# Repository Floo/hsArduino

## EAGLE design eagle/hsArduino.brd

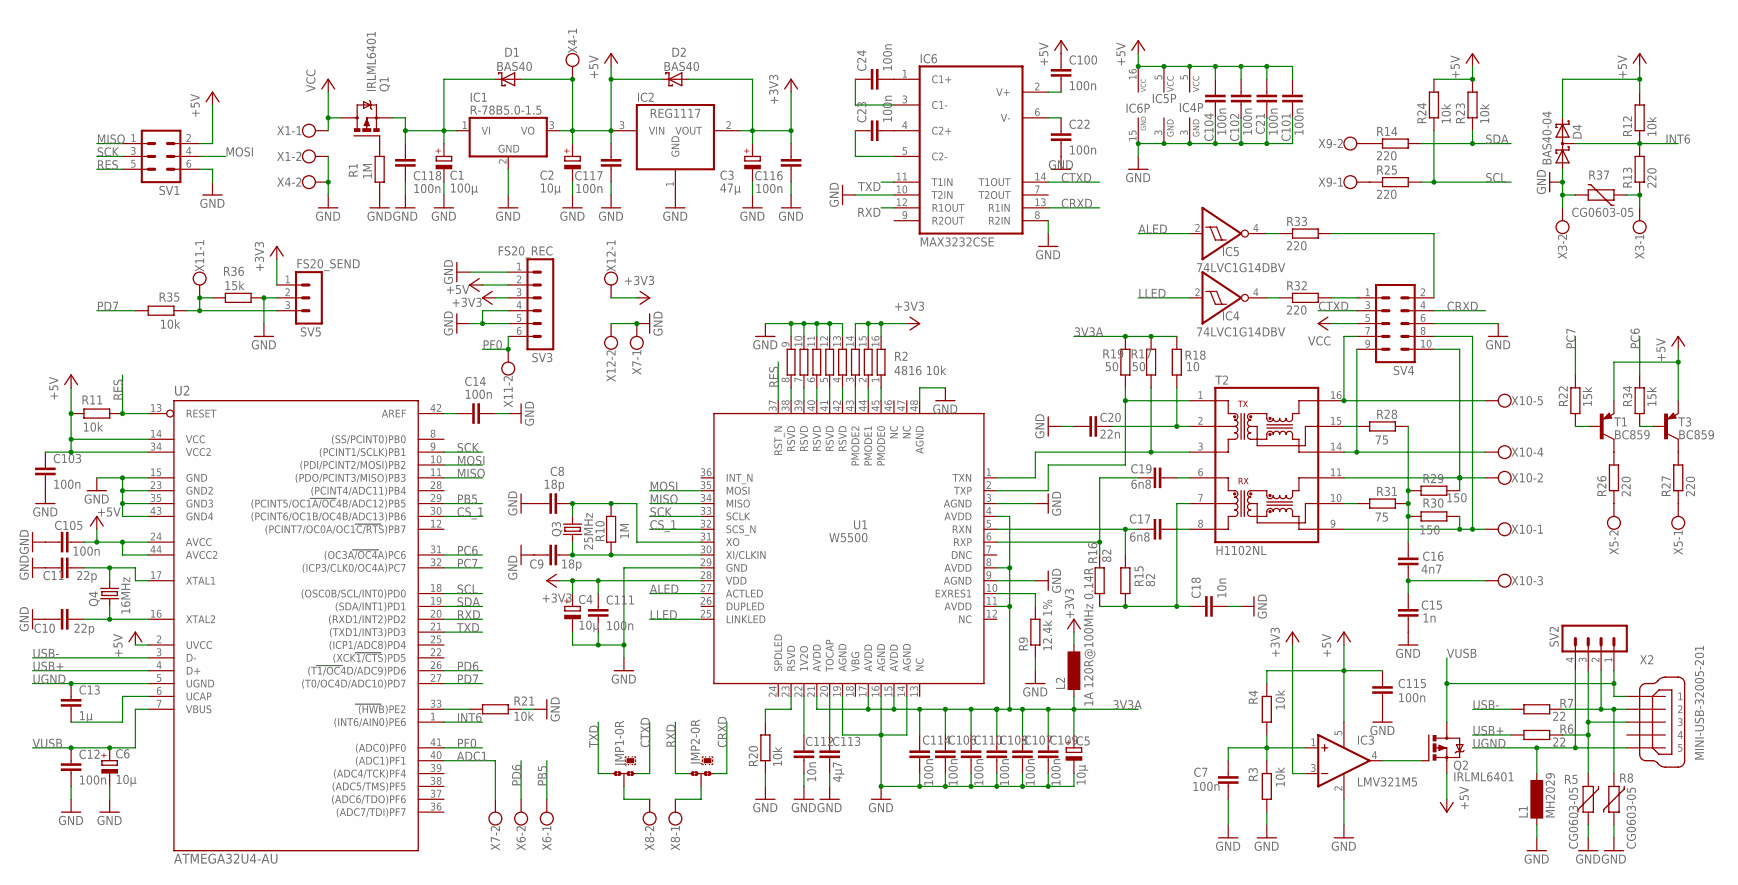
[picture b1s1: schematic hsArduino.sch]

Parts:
C1: 100µ; E2,5-7
C2, C4, C5, C6: 10µ; E2-5
C3: 47µ; E2-5
C7, C12, C14, C21, C22, C23, C24, C100, C101, C102, C103, C104, C105, C106, C107, C108, C109, C110, C111, C114, C115, C116, C117, C118: 100n; C0805K
C8, C9: 18p; C0805K
C10, C11: 22p; C0805K
C13: 1µ; C0805K
C15: 1n; C0805K
C16: 4n7; C0805K
C17, C19: 6n8; C0805K
C18, C112: 10n; C0805K
C20: 22n; C0805K
C113: 4µ7; C0805K
D1, D2: BAS40; SOT23
D4: BAS40-04; SOT23
IC1: R-78B5.0-1.5; TO220V
IC2: REG1117; SOT223
IC3: LMV321M5; SOT23-5
IC4, IC5: 74LVC1G14DBV; SOT23-5
IC6: MAX3232CSE; SO16
JMP1, JMP2: 0R-JUMPA; A0R-JMP
L1: MH2029; SM-1206
L2: 1A 120R@100MHz 0.14R; SM-1206
Q1, Q2: IRLML6401; MICRO3
Q3: 25MHz; HC49/S
Q4: 16MHz; HC49/S
R1, R10: 1M; R0805
R2: 4816 10k; 4816P
R3, R4, R11, R12, R20, R21, R23, R24, R35: 10k; R0805
R5, R8, R37: CG0603-05; CT/CN0603
R6, R7: 22; R0805
R9: 12.4k 1%; R0805
R13, R14, R25, R26, R27, R32, R33: 220; R0805
R15, R16: 82; R0805
R17, R19: 50; R0805
R18: 10; R0805
R22, R34, R36: 15k; R0805
R28, R31: 75; R0805
R29, R30: 150; R0805
SV1: ML6
SV2: MA04-1
SV3: FS20_REC; MA06-1
SV4: ML10
SV5: FS20_SEND; MA03-1
T1, T3: BC859; SOT23-BEC
T2: H1102NL; HXXXX
U1: W5500
U2: ATMEGA32U4-AU; TQFP44
X1, X3, X4, X5, X6, X7, X8, X9, X11, X12: W237-02P; W237-132
X2: MINI-USB-32005-201; 32005-201
X10: W237-05P; W237-5P

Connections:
3V3A: C5.+, C106.1, C107.1, C108.1, C109.1, C110.1, C114.1, L2.1, R17.2, R18.2, R19.2, U1.4 (AVDD), U1.8 (AVDD), U1.11 (AVDD), U1.15 (AVDD), U1.17 (AVDD), U1.21 (AVDD)
+3V3: C3.+, C4.+, C111.1, C116.2, D2.1 (A), IC2.2 (VOUT), IC3.3 (-IN), L2.2, R2.14, R2.15, R2.16, SV3.3, SV5.1, U1.28 (VDD), X12.1
+5V: C2.+, C21.1, C100.1, C101.1, C102.2, C103.1, C104.2, C105.1, C115.2, C117.2, D1.1 (A), D2.3 (C), D4.2 (C2), IC1.3 (VO), IC2.3 (VIN), IC3.5 (V+), IC4.5 (VCC), IC5.5 (VCC), IC6.16 (VCC), Q2.2 (S), R4.1, R11.2, R12.2, R23.2, R24.2, SV1.2, SV3.2, T1.E, T3.E, U2.2 (UVCC), U2.14 (VCC), U2.24 (AVCC), U2.34 (VCC2), U2.44 (AVCC2), X4.1
ADC1: U2.40 ((ADC1)PF1), X7.2
ALED: IC5.2 (I), U1.27 (ACTLED)
CRXD: IC6.13 (R1IN), JMP2.1, SV4.4
CS_1: U1.32 (SCS_N), U2.30 ((PCINT6/OC1B/OC4B/ADC13)PB6)
CTXD: IC6.14 (T1OUT), JMP1.1, SV4.3
GND: C1.-, C2.-, C3.-, C4.-, C5.-, C6.-, C7.2, C8.1, C9.2, C10.2, C11.1, C12.2, C14.2, C15.1, C18.2, C20.1, C21.2, C22.2, C101.2, C102.1, C103.2, C104.1, C105.2, C106.2, C107.2, C108.2, C109.2, C110.2, C111.2, C112.2, C113.2, C114.2, C115.1, C116.1, C117.1, C118.2, D4.1 (A1), IC1.2 (GND), IC2.1 (GND), IC3.2 (V-), IC4.3 (GND), IC5.3 (GND), IC6.8 (R2IN), IC6.10 (T2IN), IC6.15 (GND), L1.1, R1.2, R2.9, R2.10, R2.11, R2.12, R2.13, R3.2, R5.2, R8.2, R9.1, R20.1, R21.2, R36.1, R37.2, SV1.6, SV3.1, SV3.4, SV3.5, SV4.6, SV5.2, U1.3 (AGND), U1.9 (AGND), U1.14 (AGND), U1.16 (AGND), U1.19 (AGND), U1.29 (GND), U1.48 (AGND), U2.15 (GND), U2.23 (GND2), U2.35 (GND3), U2.43 (GND4), X1.2, X3.2, X4.2, X7.1, X12.2
INT6: D4.3 (C1A2), R12.1, R13.2, U2.1 ((INT6/AIN0)PE6)
LLED: IC4.2 (I), U1.25 (LINKLED)
MISO: SV1.1, U1.34 (MISO), U2.11 ((PDO/PCINT3/MISO)PB3)
MOSI: SV1.4, U1.35 (MOSI), U2.10 ((PDI/PCINT2/MOSI)PB2)
unnamed: C10.1, Q4.2, U2.16 (XTAL2)
unnamed: C11.2, Q4.1, U2.17 (XTAL1)
unnamed: C17.1, R15.1, U1.5 (RXN)
unnamed: C1.+, C118.1, D1.3 (C), IC1.1 (VI), Q1.2 (S)
unnamed: C113.1, U1.20 (TOCAP)
unnamed: C19.1, R16.1, U1.6 (RXP)
unnamed: C9.1, Q3.2, R10.2, U1.30 (XI/CLKIN)
unnamed: R35.1, R36.2, SV5.3, X11.1
unnamed: JMP1.2, X8.2
unnamed: C20.2, R18.1, T2.2
unnamed: Q1.1 (G), R1.1
unnamed: C8.2, Q3.1, R10.1, U1.31 (XO)
unnamed: R19.1, T2.1, U1.2 (TXP)
unnamed: R2.8, U1.38 (RSVD)
unnamed: R20.2, U1.23 (RSVD)
unnamed: C18.1, R15.2, R16.2, T2.7
unnamed: R17.1, T2.3, U1.1 (TXN)
unnamed: C19.2, T2.6
unnamed: SV4.7, T2.16, X10.5
unnamed: C112.1, U1.22 (1V2O)
unnamed: SV4.9, T2.14, X10.4
unnamed: R29.1, SV4.10, T2.11, X10.2
unnamed: R28.2, T2.15
unnamed: C15.2, C16.1, X10.3
unnamed: R2.7, U1.39 (RSVD)
unnamed: JMP2.2, X8.1
unnamed: R33.2, SV4.2
unnamed: R9.2, U1.10 (EXRES1)
unnamed: C14.1, U2.42 (AREF)
unnamed: R2.6, U1.40 (RSVD)
unnamed: R2.5, U1.41 (RSVD)
unnamed: R2.4, U1.42 (RSVD)
unnamed: C17.2, T2.8
unnamed: R2.3, U1.43 (PMODE2)
unnamed: R2.2, U1.44 (PMODE1)
unnamed: R2.1, U1.45 (PMODE0)
unnamed: C16.2, R28.1, R29.2, R30.2, R31.1
unnamed: R13.1, R37.1, X3.1
unnamed: R31.2, T2.10
unnamed: R30.1, SV4.8, T2.9, X10.1
unnamed: IC5.4 (O), R33.1
unnamed: IC4.4 (O), R32.1
unnamed: R21.1, U2.33 ((HWB)PE2)
unnamed: R26.1, X5.2
unnamed: R32.2, SV4.1
unnamed: R27.1, X5.1
unnamed: C24.1, IC6.3 (C1-)
unnamed: R7.1, R8.1, SV2.2, X2.2
unnamed: C24.2, IC6.1 (C1+)
unnamed: C23.2, IC6.4 (C2+)
unnamed: C23.1, IC6.5 (C2-)
unnamed: C22.1, IC6.6 (V-)
unnamed: C100.2, IC6.2 (V+)
unnamed: R26.2, T1.C
unnamed: R5.1, R6.1, SV2.3, X2.3
unnamed: R27.2, T3.C
unnamed: R22.1, T1.B
unnamed: R34.1, T3.B
unnamed: C13.2, U2.6 (UCAP)
unnamed: C7.1, IC3.1 (+IN), R3.1, R4.2
unnamed: IC3.4 (OUT), Q2.1 (G)
unnamed: R14.1, X9.2
unnamed: R25.1, X9.1
PB5: U2.29 ((PCINT5/OC1A/OC4B/ADC12)PB5), X6.1
PC6: R34.2, U2.31 ((OC3A/OC4A)PC6)
PC7: R22.2, U2.32 ((ICP3/CLK0/OC4A)PC7)
PD6: U2.26 ((T1/OC4D/ADC9)PD6), X6.2
PD7: R35.2, U2.27 ((T0/OC4D/ADC10)PD7)
PF0: SV3.6, U2.41 ((ADC0)PF0), X11.2
RES: R11.1, SV1.5, U1.37 (RST_N), U2.13 (RESET)
RXD: IC6.12 (R1OUT), JMP2.3, U2.20 ((RXD1/INT2)PD2)
SCK: SV1.3, U1.33 (SCLK), U2.9 ((PCINT1/SCLK)PB1)
SCL: R24.1, R25.2, U2.18 ((OSC0B/SCL/INT0)PD0)
SDA: R14.2, R23.1, U2.19 ((SDA/INT1)PD1)
TXD: IC6.11 (T1IN), JMP1.3, U2.21 ((TXD1/INT3)PD3)
UGND: C13.1, L1.2, SV2.4, U2.5 (UGND), X2.5
USB+: R6.2, U2.4 (D+)
USB-: R7.2, U2.3 (D-)
VCC: Q1.3 (D), SV4.5, X1.1
VUSB: C6.+, C12.1, Q2.3 (D), SV2.1, U2.7 (VBUS), X2.1

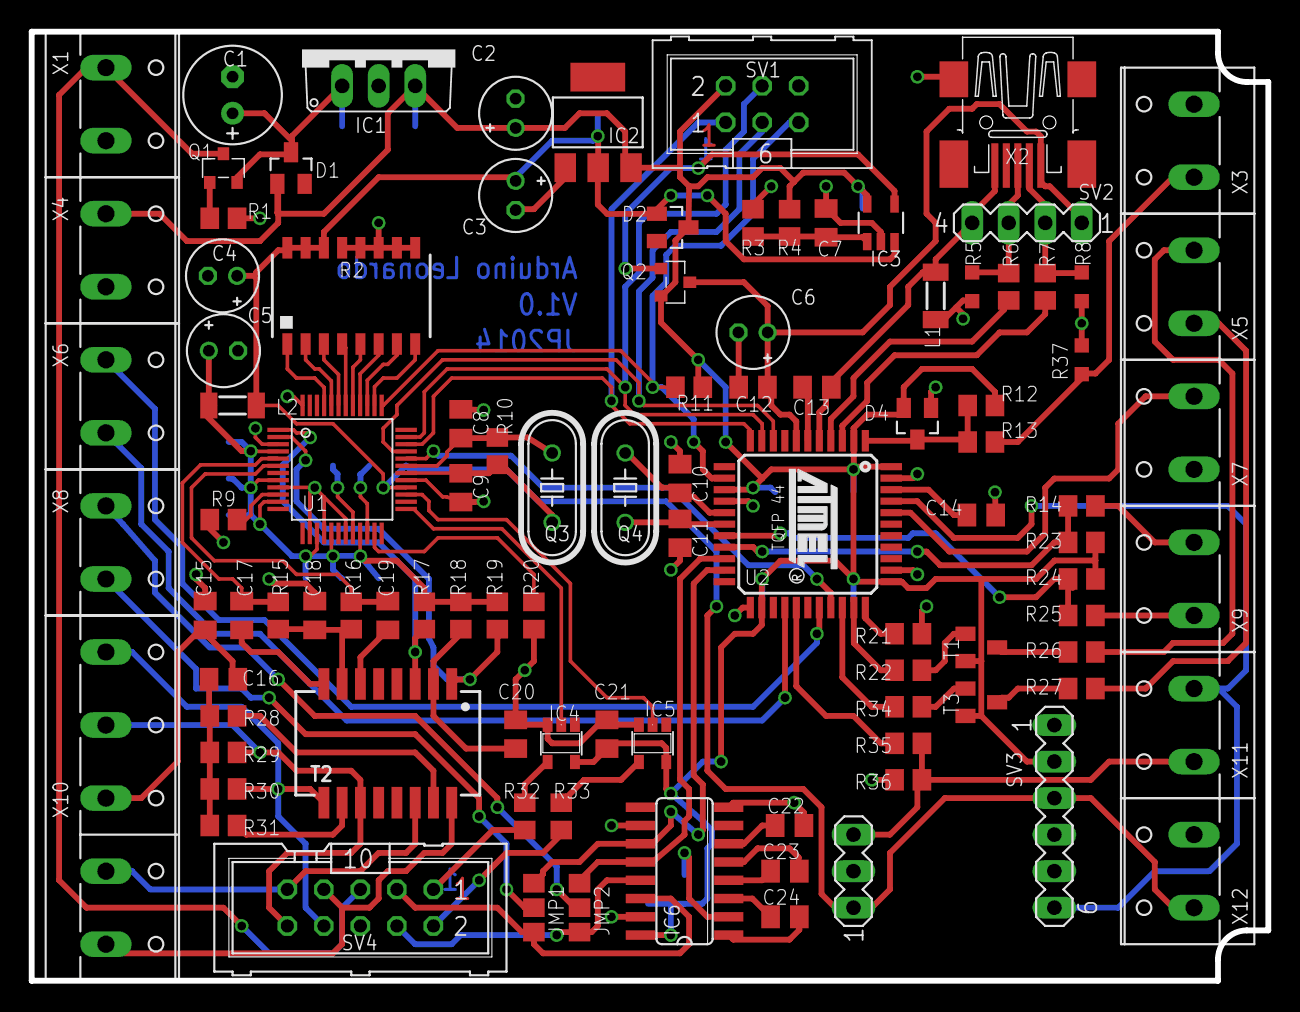
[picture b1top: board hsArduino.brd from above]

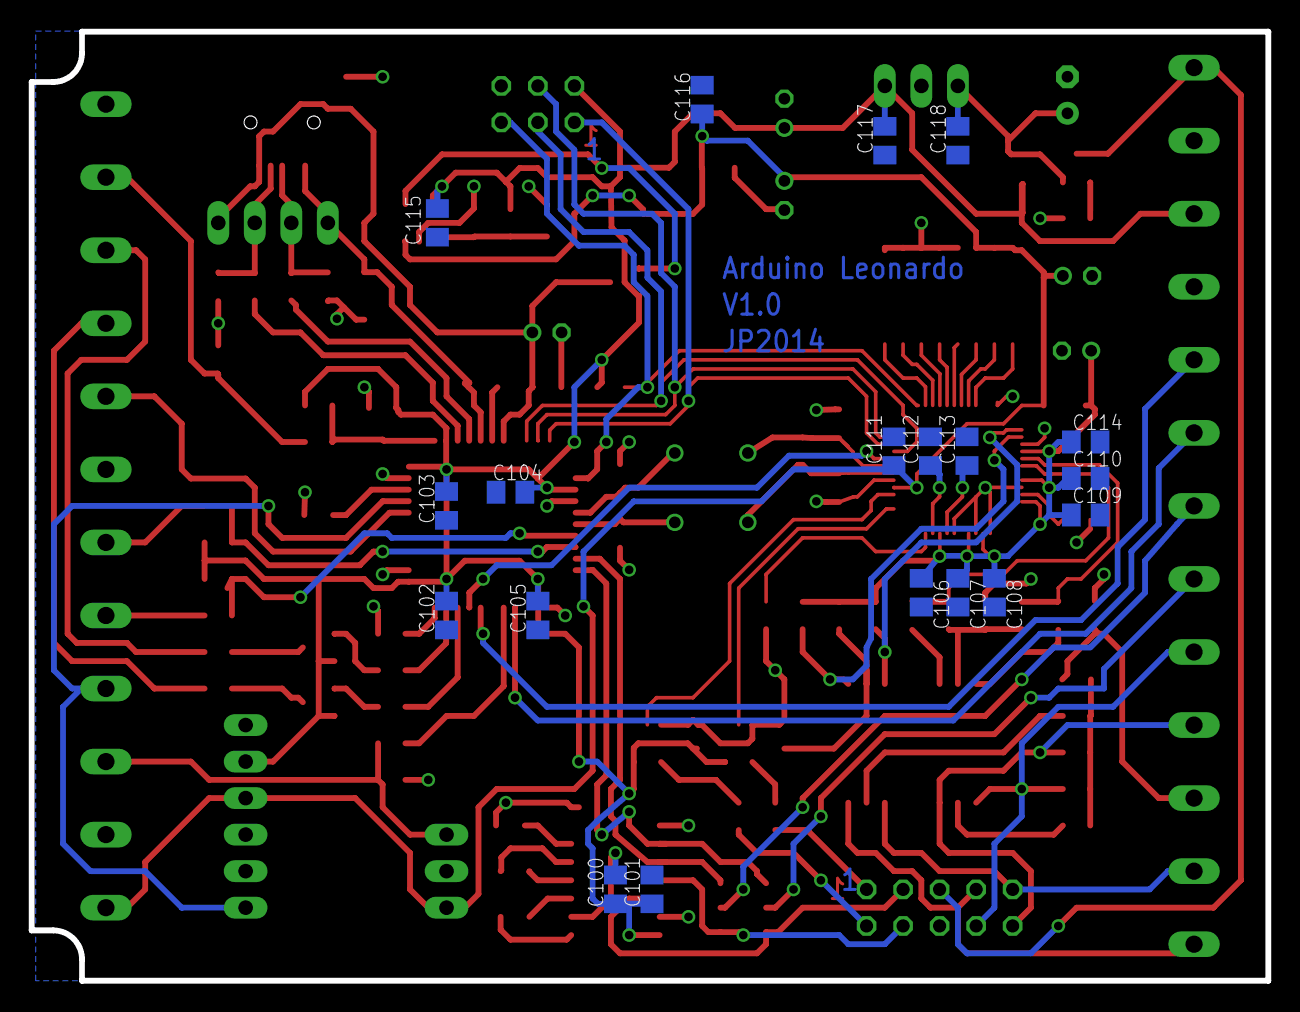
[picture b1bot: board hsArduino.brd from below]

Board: 2 copper layers, 86.0 x 66.0 mm, 119 parts (19 on the bottom side), 93 nets.

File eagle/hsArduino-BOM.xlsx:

Anzahl | Part | Value | Package | Sonstiges | Conrad-Best.-Nr. | Conrad-Preis | Reichelt-Best.Nr. | Reichelt-Preis | Segor-Best.-Nr. | Segor-Preis | Mouser-Best.-Nr. | Mouser-Preis | Preis pro Einheit
2 | C8, C9 | 18p | 0805 |  |  |  | NPO-G0805 18P | 0.05 |  |  |  |  | 0.1
2 | C11, C12 | 22p | 0805 |  |  |  | NPO-G0805 22P | 0.05 |  |  |  |  | 0.1
1 | C15 | 1n | 0805 |  |  |  | X7R-G0805 1N | 0.05 |  |  |  |  | 0.05
1 | C16 | 4n7 | 0805 |  |  |  | X7R-G0805 4,7N | 0.05 |  |  |  |  | 0.05
2 | C17, C19 | 6n8 | 0805 |  |  |  | X7R-G0805 6,8N | 0.05 |  |  |  |  | 0.1
2 | C18, C112 | 10n | 0805 |  |  |  | X7R-G0805 10N | 0.05 |  |  |  |  | 0.1
1 | C20 | 22n | 0805 |  |  |  | X7R-G0805 22N | 0.05 |  |  |  |  | 0.05
24 | C7, C12, C14, C21, C22, C23, C24, C100, C101, C102, C103, C104, C105, C106, C10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 | 100n | 0805 |  |  |  | X7R-G0805 100N | 0.05 |  |  |  |  | 1.2000000000000002
1 | C13 | 1µ | 0805 |  |  |  | X7R-G0805 1,0/25 | 0.05 |  |  |  |  | 0.05
1 | C113 | 4µ7 | 0805 |  |  |  | X7R-G0805 4,7/25 | 0.05 |  |  |  |  | 0.05
4 | C2, C4, C5, C6 | 10µ | RM2/5 |  |  |  | RAD 10/35 | 0.04 |  |  |  |  | 0.16
 | C3 | 47µ | RM2/5 |  |  |  | RAD 47/16 | 0.04 |  |  |  |  | 0
 | C1 | 100µ | RM2,5/7 |  |  |  | RAD 100/25 | 0.04 |  |  |  |  | 0
1 | R18 | 10 | 0805 |  |  |  |  | 0.08 |  |  |  |  | 0.08
2 | R6, R7 | 22 | 0805 |  |  |  |  | 0.08 |  |  |  |  | 0.16
2 | R17, R19 | 50 | 0805 |  |  |  |  | 0.08 |  |  |  |  | 0.16
2 | R28, R31 | 75 | 0805 |  |  |  |  | 0.08 |  |  |  |  | 0.16
2 | R15, R16 | 82 | 0805 |  |  |  |  | 0.08 |  |  |  |  | 0.16
2 | R29, R30 | 150 | 0805 |  |  |  |  | 0.08 |  |  |  |  | 0.16
7 | R13, R14, R25, R26, R27, R32, R33 | 220 | 0805 |  |  |  |  | 0.08 |  |  |  |  | 0.56000000000000005
9 | R3, R4, R11, R12, R20, R21, R23, R24, R35 | 10k | 0805 |  |  |  |  | 0.08 |  |  |  |  | 0.72
1 | R9 | 12.4k 1% | 0805 |  |  |  |  | 0.08 |  |  |  |  | 0.08
3 | R22, R34, R36 | 15k | 0805 |  |  |  |  | 0.08 |  |  |  |  | 0.24
2 | R1, R10 | 1M | 0805 |  |  |  |  | 0.08 |  |  |  |  | 0.16
1 | R2 | 4816 10k | BOURNS RESISTOR NETWORK |  |  |  |  |  |  |  | 652-4816P-1LF-10K | 0.85 | 0.85
3 | R5, R8, R37 | CG0603-05 | 0603 | Varistor |  |  |  |  |  |  | 652-CG0603MLU-05E | 0.26 | 0.78
1 | L1 | MH2029 | Inductor |  |  |  |  |  |  |  | 652-MH2029-100Y | 0.09 | 0.09
1 | L2 | 1A 120R@100MHz 0.14R | Inductor |  |  |  |  |  |  |  | 652-MH2029-121Y | 0.09 | 0.09 | Woher??
1 | IC6 | MAX3232CSE | NarrowSO16 |  |  |  | MAX 3232 CSE | 1.1000000000000001 |  |  |  |  | 1.1000000000000001
2 | Q1, Q2 | IRLML6401 | MICRO3 |  |  |  | IRLML6401 | 0.15 |  |  |  |  | 0.3
1 | T2 | H1102NL |  |  |  |  |  |  |  |  | 673-H1102FNL | 4.33 | 4.33
1 | IC2 | TS1117CW-3.3 | SOT223 |  |  |  | TS 1117 BCW33 | 0.3 |  |  |  |  | 0.3
1 | IC1 | R-78B5.0-1.5 |  |  |  |  |  |  |  |  | 919-R-78B5.0-1.0 | 6.96 | 6.96 | 1 A??
1 | Q3 | 25MHz HC49 | LowProfile |  |  |  | 25,0000-HC49U-S | 0.17 |  |  |  |  | 0.17
1 | Q4 | 16MHz HC49 | LowProfile |  |  |  | 16,0000-HC49U-S | 0.14000000000000001 |  |  |  |  | 0.14000000000000001
2 | T1, T3 | BC859(BC807-40) |  |  |  |  | BC 859C SMD | 0.04 |  |  |  |  | 0.08
2 | D1, D2 | BAS40 | SOT-23 |  |  |  | BAS 40 SMD | 7.0000000000000007E-2 |  |  |  |  | 0.14000000000000001
1 | D4 | BAS40-04 | SOT-23 |  |  |  | BAS 40-04 SMD | 0.05 |  |  |  |  | 0.05
1 | U1 | W5500 |  |  |  |  |  |  |  |  | 950-W5500 | 2.69 | 2.69
1 | U2 | ATMEGA32U4-AU |  |  |  |  |  |  |  |  | 556-ATMEGA32U4-AU | 5.13 | 5.13
1 | IC3 | LMV321M5 | SOT23-5 |  |  |  |  |  |  |  | 926-LMV321M5/NOPB | 0.7 | 0.7
2 | IC4, IC5 | 74LVC1G14DBV | SOT23-5 |  |  |  |  |  |  |  | 595-SN74LVC1G14DBVR | 0.41 | 0.82
1 | SV1 | Wanne 6pol |  |  |  |  | WSL6G | 0.16 |  |  |  |  | 0.16
1 | SV4 | Wanne 10pol |  |  |  |  | WSL10G | 0.08 |  |  |  |  | 0.08
1 |  | Phoenix2pol |  |  |  | 0.56000000000000005 |  |  |  |  |  |  | 0.56000000000000005
1 |  | Phoenix3pol |  |  |  | 0.85 |  |  |  |  |  |  | 0.85
1 |  | Phoenix12pol |  |  |  | 3.37 |  |  |  |  |  |  | 3.37
1 |  | Phoenix8pol |  |  |  | 2.2400000000000002 |  |  |  |  |  |  | 2.2400000000000002
 |  |  |  |  |  |  |  |  |  |  |  |  | 36.630000000000003

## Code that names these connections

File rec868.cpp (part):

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void rec868_stop(void)
{
#ifdef DEBUG_PB1_ENABLE
  PORTB &= ~(1 << PB1); //Clear PB1: REC Signalisierung abschalten
#endif
  ACSR &= ~_BV(ACIE); //Interrupt ANALOG_COMP sperren
}
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  //PinChangeInt init

  //Pins ueber E6-Fkten festlegen
  //DDRD &= ~(1<<PD6); //Pin PD6 als Eingang
  //PCMSK3 = _BV(PCINT30); //PinChange fuer PCINT30 (PD6) freigeben

  /* configure port pin for use as input to the analoge comparator */
  //DDR_CONFIG_IN(FS20_RECV);
  //PIN_CLEAR(FS20_RECV);
  //Pins ueber E6-Fkten festlegen
  DDRF &= ~(1 << PF0); //Pin PF0 als Eingang
  PORTF &= ~(1 << PF0); //Clear PF0
#ifdef DEBUG_PB1_ENABLE
  //fuer Tests PB1 als Ausgang
  DDRB |= (1 << PB1);
  PORTB |= (1 << PB1);
#endif
  /* enable analog comparator,
   * use fixed voltage reference (1V, connected to AIN0)
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{
  ic_error(); //Variablen ruecksetzen
#ifdef DEBUG_PB1_ENABLE
  //PORTB |= (1<<PB1); //Set PB1: REC Signalisierung einschalten
#endif
  rec868_global.kommando = REC868_CLR;
  ACSR &= ~_BV(ACI); //anstehende Interrupts löschen
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void ic_error(void)
{
#ifdef DEBUG_PB1_ENABLE
  //PORTB &= ~(1<<PB1); //Clear PB1: REC Signalisierung abschalten
#endif
  rec868_global.fsrec = FALSE;
  rec868_global.wsrec = FALSE;
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}


/******* Interruptroutine für Analog_Comparator and AIN1 (PB3)
    Comperator bezogen auf Bandgap-Ref. (1V)
	Auswertung der Impulsfolgen *********/

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  }
  // H/L-Flanke detektiert
#ifdef DEBUG_PB1_ENABLE
  //PORTB |= (1<<PB1); //Set PB1: REC Signalisierung einschalten
#endif
  rec868_global.th = rec868_global.ttemp; //Dauer des H-Pegels (Sender-An-Dauer)
  // Beginn der Auswertung
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          rec868_global.wspre = FALSE; // Ende der Präambel
          rec868_global.bitcount = 0;
#ifdef DEBUG_PB1_ENABLE
          PORTB |= (1 << PB1); //Set PB1: REC Signalisierung einschalten
#endif
          return;
        }
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      if (rec868_global.bitcount > 6)  // Ende der Präambel
      {
#ifdef DEBUG_PB1_ENABLE
        //PORTB |= (1<<PB1); //Set PB1: REC Signalisierung einschalten
#endif
        rec868_global.fspre = FALSE;
        rec868_global.bitcount = 0;
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
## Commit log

2014-09-05 Eagle-Dateien hinzugefügt
2014-09-08 weiter programmiert
2014-09-09 alle Funktionen ergänzt

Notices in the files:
rec868.cpp:
Copyright (c) 2010 by Jens Prager <jprager@online.de>
modify it under the terms of the GNU General Public License
For more information on the GPL, please go to:
http://www.gnu.org/copyleft/gpl.html
